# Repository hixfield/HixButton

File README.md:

# HixButton

![Build with PlatformIO](https://img.shields.io/badge/build%20with-PlatformIO-orange?logo=data%3Aimage%2Fsvg%2Bxml%3Bbase64%2CPHN2ZyB3aWR0aD0iMjUwMCIgaGVpZ2h0PSIyNTAwIiB2aWV3Qm94PSIwIDAgMjU2IDI1NiIgeG1sbnM9Imh0dHA6Ly93d3cudzMub3JnLzIwMDAvc3ZnIiBwcmVzZXJ2ZUFzcGVjdFJhdGlvPSJ4TWlkWU1pZCI+PHBhdGggZD0iTTEyOCAwQzkzLjgxIDAgNjEuNjY2IDEzLjMxNCAzNy40OSAzNy40OSAxMy4zMTQgNjEuNjY2IDAgOTMuODEgMCAxMjhjMCAzNC4xOSAxMy4zMTQgNjYuMzM0IDM3LjQ5IDkwLjUxQzYxLjY2NiAyNDIuNjg2IDkzLjgxIDI1NiAxMjggMjU2YzM0LjE5IDAgNjYuMzM0LTEzLjMxNCA5MC41MS0zNy40OUMyNDIuNjg2IDE5NC4zMzQgMjU2IDE2Mi4xOSAyNTYgMTI4YzAtMzQuMTktMTMuMzE0LTY2LjMzNC0zNy40OS05MC41MUMxOTQuMzM0IDEzLjMxNCAxNjIuMTkgMCAxMjggMCIgZmlsbD0iI0ZGN0YwMCIvPjxwYXRoIGQ9Ik0yNDkuMzg2IDEyOGMwIDY3LjA0LTU0LjM0NyAxMjEuMzg2LTEyMS4zODYgMTIxLjM4NkM2MC45NiAyNDkuMzg2IDYuNjEzIDE5NS4wNCA2LjYxMyAxMjggNi42MTMgNjAuOTYgNjAuOTYgNi42MTQgMTI4IDYuNjE0YzY3LjA0IDAgMTIxLjM4NiA1NC4zNDYgMTIxLjM4NiAxMjEuMzg2IiBmaWxsPSIjRkZGIi8+PHBhdGggZD0iTTE2MC44NjkgNzQuMDYybDUuMTQ1LTE4LjUzN2M1LjI2NC0uNDcgOS4zOTItNC44ODYgOS4zOTItMTAuMjczIDAtNS43LTQuNjItMTAuMzItMTAuMzItMTAuMzJzLTEwLjMyIDQuNjItMTAuMzIgMTAuMzJjMCAzLjc1NSAyLjAxMyA3LjAzIDUuMDEgOC44MzdsLTUuMDUgMTguMTk1Yy0xNC40MzctMy42Ny0yNi42MjUtMy4zOS0yNi42MjUtMy4zOWwtMi4yNTggMS4wMXYxNDAuODcybDIuMjU4Ljc1M2MxMy42MTQgMCA3My4xNzctNDEuMTMzIDczLjMyMy04NS4yNyAwLTMxLjYyNC0yMS4wMjMtNDUuODI1LTQwLjU1NS01Mi4xOTd6TTE0Ni41MyAxNjQuOGMtMTEuNjE3LTE4LjU1Ny02LjcwNi02MS43NTEgMjMuNjQzLTY3LjkyNSA4LjMyLTEuMzMzIDE4LjUwOSA0LjEzNCAyMS41MSAxNi4yNzkgNy41ODIgMjUuNzY2LTM3LjAxNSA2MS44NDUtNDUuMTUzIDUxLjY0NnptMTguMjE2LTM5Ljc1MmE5LjM5OSA5LjM5OSAwIDAgMC05LjM5OSA5LjM5OSA5LjM5OSA5LjM5OSAwIDAgMCA5LjQgOS4zOTkgOS4zOTkgOS4zOTkgMCAwIDAgOS4zOTgtOS40IDkuMzk5IDkuMzk5IDAgMCAwLTkuMzk5LTkuMzk4em0yLjgxIDguNjcyYTIuMzc0IDIuMzc0IDAgMSAxIDAtNC43NDkgMi4zNzQgMi4zNzQgMCAwIDEgMCA0Ljc0OXoiIGZpbGw9IiNFNTcyMDAiLz48cGF0aCBkPSJNMTAxLjM3MSA3Mi43MDlsLTUuMDIzLTE4LjkwMWMyLjg3NC0xLjgzMiA0Ljc4Ni01LjA0IDQuNzg2LTguNzAxIDAtNS43LTQuNjItMTAuMzItMTAuMzItMTAuMzItNS42OTkgMC0xMC4zMTkgNC42Mi0xMC4zMTkgMTAuMzIgMCA1LjY4MiA0LjU5MiAxMC4yODkgMTAuMjY3IDEwLjMxN0w5NS44IDc0LjM3OGMtMTkuNjA5IDYuNTEtNDAuODg1IDIwLjc0Mi00MC44ODUgNTEuODguNDM2IDQ1LjAxIDU5LjU3MiA4NS4yNjcgNzMuMTg2IDg1LjI2N1Y2OC44OTJzLTEyLjI1Mi0uMDYyLTI2LjcyOSAzLjgxN3ptMTAuMzk1IDkyLjA5Yy04LjEzOCAxMC4yLTUyLjczNS0yNS44OC00NS4xNTQtNTEuNjQ1IDMuMDAyLTEyLjE0NSAxMy4xOS0xNy42MTIgMjEuNTExLTE2LjI4IDMwLjM1IDYuMTc1IDM1LjI2IDQ5LjM2OSAyMy42NDMgNjcuOTI2em0tMTguODItMzkuNDZhOS4zOTkgOS4zOTkgMCAwIDAtOS4zOTkgOS4zOTggOS4zOTkgOS4zOTkgMCAwIDAgOS40IDkuNCA5LjM5OSA5LjM5OSAwIDAgMCA5LjM5OC05LjQgOS4zOTkgOS4zOTkgMCAwIDAtOS4zOTktOS4zOTl6bS0yLjgxIDguNjcxYTIuMzc0IDIuMzc0IDAgMSAxIDAtNC43NDggMi4zNzQgMi4zNzQgMCAwIDEgMCA0Ljc0OHoiIGZpbGw9IiNGRjdGMDAiLz48L3N2Zz4=)

A simple fully designed ESP8266 WIFI button.
With schematic, PCB layout and the 3D printed case.

[See it on thingiverse](https://www.thingiverse.com/thing:4697256)

[See it on youtube](https://youtu.be/lKFYbrJro3M)

|  |  |  |
|---|---|---|
|    |  |  |
|Case ESP side|Case header side|Fuly assembled|

## Features

- Powered by a single LiFePo4 battery (one charge lasts > 1 year)
- Onboarding charging circuit based on CN3058E powered via the FTDI connector's 5V
- Onboard power supervisor to make sure ESP does not boot (with garbage) if batery is to low
- Contains an RGB led (used to signal status back from the server e.g. heating on or off, and locally also used to signal low battery condition)
- Firmware sends a json formatted datagram (UDP)
 * to any configurable server
 * and optionally receives datagram back (UDP) to set status led (and its duration)
 * sends over battery status so server can signal low bat conditions
- Works great with Node-red e.g. running on Raspberry Pi
- Solder jumper to keep module awake (during debugging)
- Puts the ESP in a deep sleep after pressing the button to conserve battery power.
- Fast WiFi connection establish techniques (e.g. fixed ip) to make button responsive
- 3D printed finished case

## Improvements

- [x] external NO connector to have external input (over RST switch) -> use it to make e.g. "I have mail in my mailbox"
- [x] External FTDI programming connector 
- [x] LiFePO4 under voltage protection
- [x] Replace the big elco cap to multiple tantilums to not be so high
- [x] connect ftdi to 5v (its not 3.3) and use this as charging connector
- [x] rgb led part no uxxx and type
- [x] charging chip no uxxx and type
- [x] adjust charging resistor
- [x] use power and signal nets in sch and then test if these are used for pcb routing
- [x] lets order a stencel for the PCB to test it :)
- [x] add LiFePO4 bat charging circutry (add external connector)
- [x] FTDI power is always 5V use this for battery charing (but limit current)
- [ ] OTA programming?

## Will not do
- [x] Put CH340 USB serial on it (to complex for once programming)
- [x] don't go to sleep if (1)FTDI plugged-in (2)charing power applied
- [x] change push switch type, the one we have should do the trick

# Hardware

[Click here for hardware information](hardware/README.md)

# Software

[Click here for software information](software/README.md)

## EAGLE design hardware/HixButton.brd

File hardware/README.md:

# Get an impression :-)
|  |  |  |
|---|---|---|
|solder paste applied|after headgun: soldered!|and bottom too|
|    |  |  |
|it works!|also ordered solder stencel|stencel and pcb|
|    |  |  |
|Case ESP side|Case header side|Fuly assembled|
# 3D printed case
You can find all requird `stl`files on [thingiverse](https://www.thingiverse.com/thing:4697256) (and in the `case` folder of this repo)

# Schematic

- LiFePO4 charging current set as `I = 1.205/R3` (schematic lists 5.6K which is approx 200mA to keep things cool)

# PCB
| Top                                 | Bottom                                 |
|-------------------------------------|----------------------------------------|
|  |  |

# BOM
|Qty|Value     |Device                 |Parts             |
|---|----------|-----------------------|------------------|
|4  |100nF     |SMD 1206               |C1, C2, C3, C4    |
|5  |100μF     |Tantalum SMD 1206      |C5, C6, C7, C8, C9|
|3  |10K       |SMD 1206               |R1, R2, R10       |
|1  |1uF       |SMD 1206               |C10               |
|1  |2.2K      |SMD 1206               |R12               |
|1  |330       |SMD 1206               |R4                |
|1  |5.6K      |SMD 1206               |R3                |
|1  |CN3058E   |CN3058E                |U3                |
|1  |ESP12E    |ESP12E                 |U1                |
|1  |FTDI      |6P Female header       |J1                |
|1  |GRN       |LED 1206 Green         |L1(GRN)           |
|1  |RED       |LED 1206 Red           |L2(RED)           |
|1  |RST       |PUSHBTNSMALL           |S3                |
|1  |TPS3839L30|TPS3839L30             |U2                |
|1  |WS2812    |LED RGB WS2812 SMD 5050|U4                |

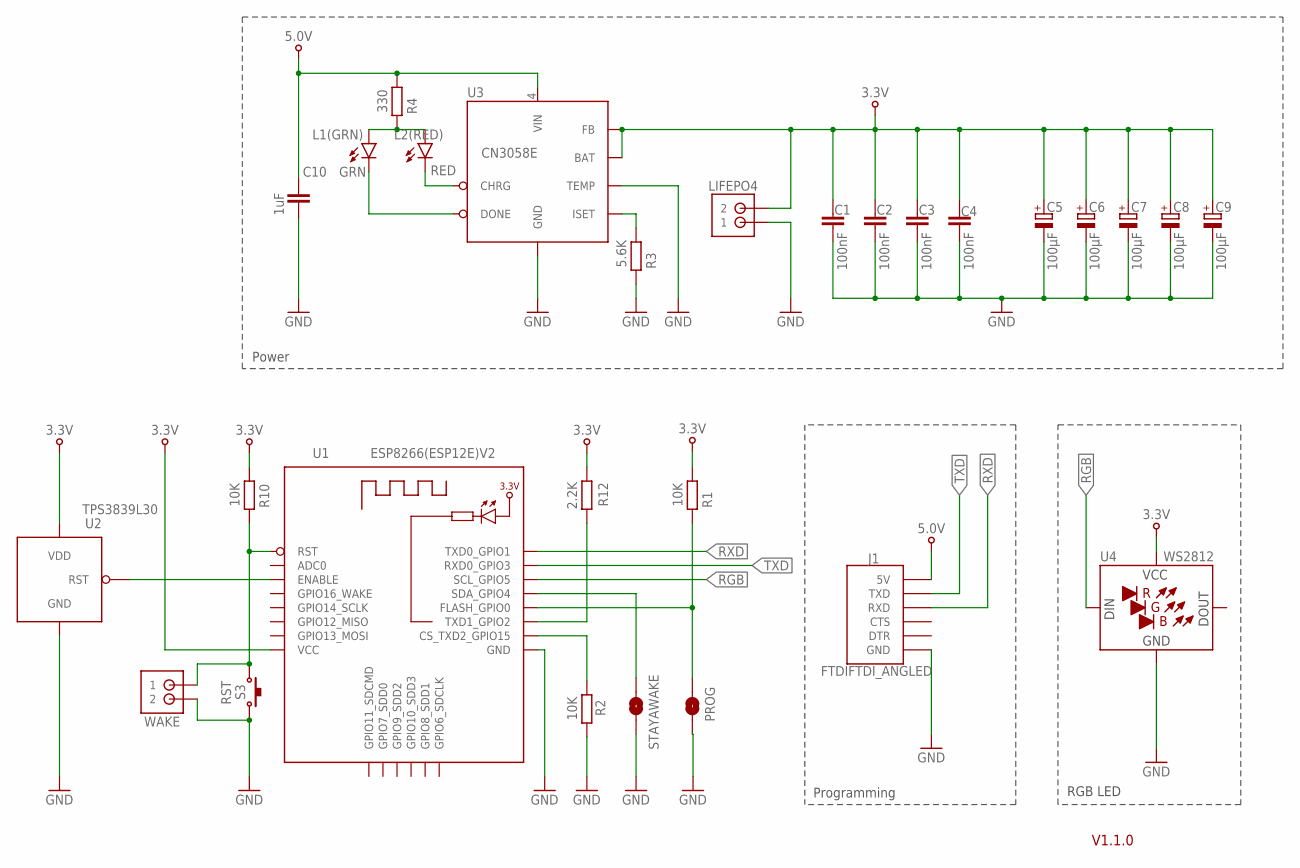
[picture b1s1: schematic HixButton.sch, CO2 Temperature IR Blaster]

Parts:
C1, C2, C3, C4: 100nF; C1206
C5, C6, C7, C8, C9: 100μF; SMC_A
C10: 1uF; C1206
J1: FTDIFTDI_ANGLED; FTDI_ANGLED
L1(GRN): GRN; CHIPLED_1206
L2(RED): RED; CHIPLED_1206
LIFEPO4: XH2P
PROG: SJ
R1, R2, R10: 10K; R1206
R3: 5.6K; R1206
R4: 330; R1206
R12: 2.2K; R1206
S3: RST; SMDPUSHBTN_TYPE1
STAYAWAKE: SJ
U1: ESP8266(ESP12E)V2; ESP8266(ESP12E)
U2: TPS3839L30; SOT23
U3: CN3058E; SOP8
U4: WS2812; LED_5050
WAKE: XH2P

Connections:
3.3V: C1.1, C2.1, C3.1, C4.1, C5.+, C6.+, C7.+, C8.+, C9.+, LIFEPO4.2, R1.2, R10.2, R12.2, U1.VCC, U2.3 (VDD), U3.5 (BAT), U3.8 (FB), U4.3 (VCC)
5.0V: C10.1, J1.5V, R4.2, U3.4 (VIN)
GND: C1.2, C2.2, C3.2, C4.2, C5.-, C6.-, C7.-, C8.-, C9.-, C10.2, J1.GND, LIFEPO4.1, PROG.1, R2.1, R3.1, S3.1, STAYAWAKE.1, U1.GND, U2.1 (GND), U3.1 (TEMP), U3.3 (GND), U4.1 (GND), WAKE.2
unnamed: R2.2, U1.GPIO15_CS_TXD2 (CS_TXD2_GPIO15)
unnamed: R12.1, U1.GPIO2_TXD1 (TXD1_GPIO2)
unnamed: PROG.2, R1.1, U1.GPIO0_FLASH (FLASH_GPIO0)
unnamed: STAYAWAKE.2, U1.GPIO4_SDA (SDA_GPIO4)
unnamed: R10.1, S3.2, U1.RST, WAKE.1
unnamed: R3.2, U3.2 (ISET)
unnamed: U1.ENABLE, U2.2 (RST)
unnamed: L1(GRN).A, L2(RED).A, R4.1
unnamed: L2(RED).C, U3.7 (CHRG)
unnamed: L1(GRN).C, U3.6 (DONE)
RGB: U1.GPIO5_SCL (SCL_GPIO5), U4.2 (DIN)
RXD: J1.RXD, U1.GPIO1_TXD0 (TXD0_GPIO1)
TXD: J1.TXD, U1.GPIO3_RXD0 (RXD0_GPIO3)

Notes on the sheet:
Power
Programming
RGB LED
V1.1.0

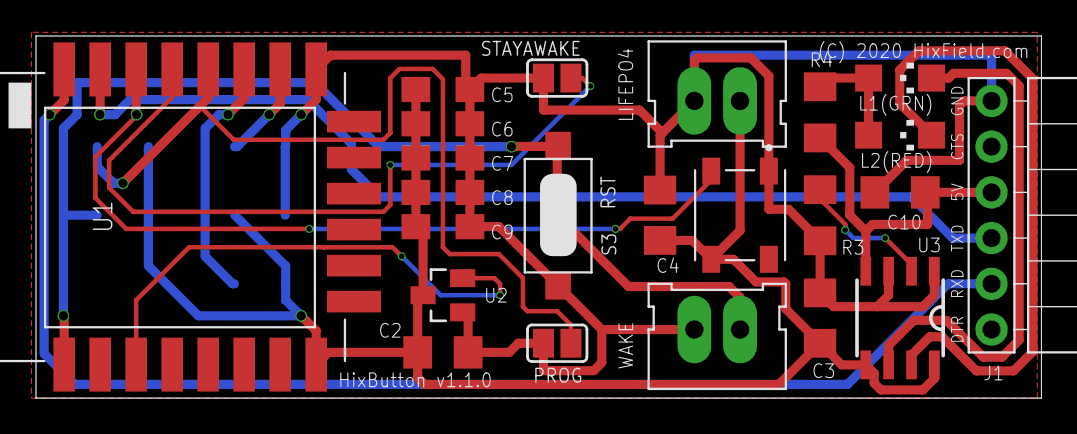
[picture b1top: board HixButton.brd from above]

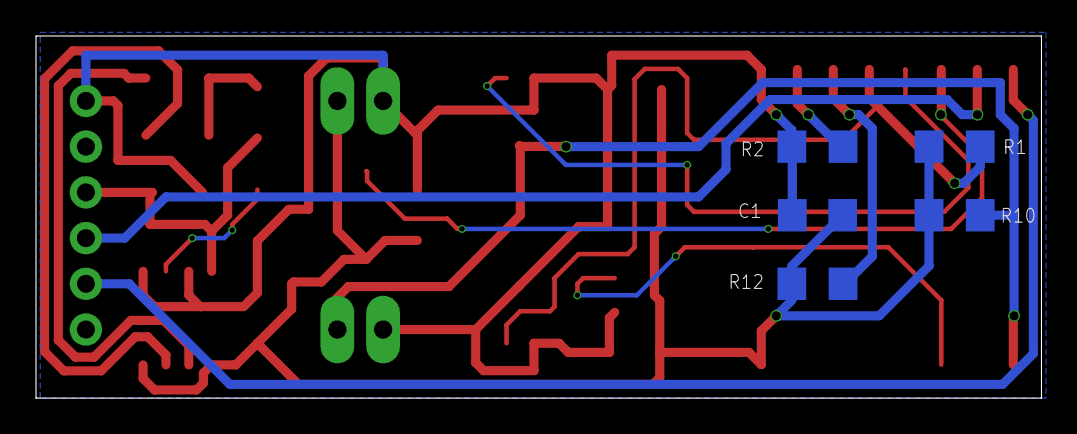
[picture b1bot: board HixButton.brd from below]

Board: 2 copper layers, 55.9 x 20.1 mm, 28 parts (5 on the bottom side), 16 nets.

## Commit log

2020-11-25 2nd commit
2020-11-27 working on config and code cleanness
2020-11-28 continued working
2020-11-28 added RGB led
2020-11-28 tweaked rgb led
2020-11-28 split hw and sw
2020-11-28 moved license file to root
2020-11-28 AP for wifi config
2020-11-29 increase ap timeout
2020-12-04 update todo readme
2020-12-06 hardware update
2020-12-06 updated hardware board and schematic
2020-12-11 updated hardware
2020-12-11 updated sch and board layout
2020-12-11 update board
2020-12-11 added dru and cam
2020-12-11 before routing
2020-12-11 routing complete
2020-12-12 orderd pcbs
2020-12-13 added bom to hardware
2020-12-18 v1.1.0 fix voltage supervisor
2020-12-18 moved rules to rules
2020-12-18 v1.1.0 production
2020-12-18 updated version number on board
2020-12-18 added cam zip
2020-12-18 updated images brd, sch
2020-12-19 added sj 3d model
2020-12-25 added hardware pictures
2020-12-26 added hardware pictures + v1.1.0 of the firmware
2020-12-26 added root icon
2020-12-26 fix update config + mDNS added
2020-12-27 added wifi_mac to datagram contents
2020-12-29 added build timestamp
2020-12-30 visual studio code update
2020-12-30 updated gitignore
2020-12-30 updated bom
2021-01-01 added led fading animations
2021-01-02 added node-RED example to readme(s)
2021-01-17 added transparant image hand pressing button

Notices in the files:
hardware/HixButton.brd:
(C) 2020 HixField.com
